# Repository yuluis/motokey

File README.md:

# MotoKey — Aftermarket E-Moto Security System

Encrypted keycard lock for electric motorcycles. Cut the power, pocket the key.

**Live site:** https://kindro.store
**Hardware design:** https://kindro.store/hardware-design.html

---

## What Is This

MotoKey is an aftermarket security system for electric mopeds/motorcycles/scooters. It's a small weatherproof box that wires inline with the battery and cuts power unless an encrypted key fob is nearby. No key = no power = bike doesn't move.

Every kit ships with:
- 1 lock box (mounts on bike, inline with battery)
- 2 encrypted key fobs (pocket/keychain sized)
- Mounting kit (bracket, zip ties, adhesive, wire terminals, heat shrink)
- Instruction card with QR link to install video

Two products:
| Product | Price | Key Difference |
|---------|-------|----------------|
| **MotoKey Basic** | $89 | AES-128, single relay, CR2032 fob, 30ft range |
| **MotoKey Enhanced** | $149 | AES-256, dual relay + tamper alert, USB-C fob, 50ft range, 3 fobs |

---

## Origin

This project started as a learning exercise between Luis and Julio on 2026-02-21. The goal: use AI (Claude) to go from idea to live website to hardware design in a single session.

**The conversation:**
- Julio builds aftermarket e-motos and wanted a keycard security system to sell
- Start with two versions: a basic remote and an enhanced remote
- Key fobs should be small (keychain/pocket dongle)
- The lock box connects to the battery with a simple power-cut circuit
- Must be weatherproof (outdoor bike use)
- Programming between keycard and hardware must be secured to prevent hacking
- Comes with 2 keys and a mounting kit

**What got built in this session:**
1. Product storefront website (static HTML/CSS/JS)
2. Full hardware architecture with real component selection
3. Security protocol design (AES-128 rolling codes, challenge-response)
4. Bill of materials with per-unit costs
5. Margin analysis proving profitability at $89/$149
6. Pushed to GitHub, deployed to production at kindro.store

---

## How It Works

### The Lock Box

Wires inline with the bike's main battery positive cable. Contains:
- **ATmega328P** microcontroller (same chip as Arduino)
- **SYN480R** 433MHz RF receiver
- **JQX-62F** 80A automotive relay (normally OPEN = locked)
- **LM2596** buck converter (48-72V battery → 5V logic)
- **AT24C256** EEPROM (stores up to 8 paired key records)
- Status LED + recessed pair button

The relay defaults to **open** (no power). When a valid key fob signal is received, the relay closes and power flows. When the key fob is out of range for 30 seconds, the relay opens and the bike is locked.

Cutting the wires doesn't help — the relay is normally open, so cutting anything just keeps the bike dead.

### The Key Fob

Small enough for a keychain. Contains:
- **ATtiny85** microcontroller (1.8μA sleep current)
- **SYN115** 433MHz RF transmitter
- **CR2032** coin cell battery (~18 month life)
- Single button

Press the button → MCU wakes from sleep → encrypts (counter + device ID) with the shared AES key → transmits 16-byte packet → goes back to sleep. Total active time: ~50ms.

### Security Protocol

**Pairing (one-time):**
1. Press PAIR button on lock box (LED blinks fast)
2. Press button on key fob
3. Lock box generates random 128-bit key
4. Key transfers to fob via physical contact (NFC/wired — can't intercept from distance)
5. Both devices store shared secret + set counter to 0

**Unlock (every use):**
1. Fob increments counter, encrypts (counter + fob ID) with shared key
2. Transmits encrypted packet over 433MHz
3. Lock box decrypts, verifies fob ID, checks counter > last seen
4. If valid: close relay (power on), start 30-sec timeout

**Why it's secure:**
- **Replay attack** → Fails. Counter already advanced. Old codes rejected.
- **Brute force** → AES-128 = 3.4×10³⁸ possible keys. Would take 10²² years at 1 billion attempts/sec.
- **Signal capture** → Every packet looks like random noise. No patterns.
- **Physical tamper** → Electronics potted in epoxy. Cracking the box destroys the circuits.
- **Wire bypass** → Relay is normally open. Cutting wires = bike stays dead.

---

## Economics

### Bill of Materials (at 100 units)

**Lock Box:** $10.80
| Component | Part | Cost |
|-----------|------|------|
| MCU | ATmega328P-AU | $1.40 |
| RF Receiver | SYN480R 433MHz | $0.50 |
| Relay | JQX-62F 80A | $2.80 |
| Relay Driver | 2N2222A + 1N4007 | $0.10 |
| Voltage Reg | LM2596 buck module | $0.80 |
| EEPROM | AT24C256 | $0.25 |
| Crystal | 16MHz + caps | $0.15 |
| LED + Button | Bicolor + tactile | $0.18 |
| Screw Terminals | 5mm pitch x2 | $0.30 |
| Wire Leads | 10AWG silicone x2 | $0.60 |
| Antenna | 17cm wire | $0.02 |
| PCB | 2-layer 50x40mm (JLCPCB) | $0.80 |
| Enclosure | ABS IP65 80x60x30mm | $1.80 |
| Cable Glands | PG7 nylon x2 | $0.20 |
| Potting | Urethane 2-part ~30ml | $0.50 |
| Misc | Caps, resistors, header | $0.40 |

**Key Fob (x1):** $2.37
| Component | Part | Cost |
|-----------|------|------|
| MCU | ATtiny85-20SU | $0.65 |
| RF Transmitter | SYN115 433MHz | $0.35 |
| Battery Holder | CR2032 SMD | $0.12 |
| Battery | CR2032 | $0.20 |
| Button | Tactile SMD 4x4mm | $0.05 |
| PCB | 2-layer 35x20mm | $0.40 |
| Enclosure | ABS fob case + keyring | $0.45 |
| Misc | Caps, resistors | $0.15 |

**Mounting Kit:** $1.60 | **Packaging:** $1.20

### Margin Analysis

| | Basic ($89) | Enhanced ($149) |
|---|---|---|
| BOM + materials | $18.34 | $31.10 |
| Assembly + QC | $5.00 | $8.25 |
| **Total COGS** | **$23.34** | **$39.35** |
| **Gross margin** | **$65.66 (73.8%)** | **$109.65 (73.6%)** |

At even 10 hand-built units ($30 COGS), the Basic still clears $59/unit.

---

## Next Steps for Julio

### Phase 1: Prototype (Weekends 1-2) — ~$35

Buy from Amazon/AliExpress:
- Arduino Nano (ATmega328P dev board) — $5
- 433MHz TX/RX module pair — $3
- 80A automotive relay module — $6
- ATtiny85 dev board (Digispark) — $4
- LM2596 buck converter module — $2
- Breadboard + jumper wires — $5
- CR2032 battery + holder — $2
- Push buttons + LEDs + resistors — $3
- ABS project box — $3
- Key fob cases (2-pack) — $2

Also need (one-time): USB-ASP programmer (~$8), soldering iron if you don't have one.

**Weekend 1: Proof of concept**
- Wire Arduino Nano + relay on breadboard
- Wire ATtiny85 + 433MHz TX on second breadboard
- Write basic TX/RX code (no encryption yet)
- Goal: press fob button → relay clicks → LED lights up

**Weekend 2: Add security**
- Add AES-128 library to both MCUs (use `tiny-AES-c` library)
- Hardcode a shared test key
- Implement rolling counter
- Verify that replaying a captured signal is rejected

### Phase 2: Complete Product (Weekends 3-4)

**Weekend 3: Pairing + polish**
- Add pair button logic on lock box
- Implement key exchange (wired connection for prototype)
- Add LED status states (green=unlocked, red=locked, blink=pairing)
- Add 30-second auto-lock timeout
- Add EEPROM storage for paired keys (support up to 8)

**Weekend 4: Enclosure + real test**
- Solder onto perfboard (replace breadboard)
- Mount in ABS project box with cable glands
- Fit fob circuit into key fob case
- Test with actual e-moto (or 48V bench supply)
- Range test through walls (target: 20-30m)
- Seal with potting compound

### Phase 3: First Production Run (Week 5-6)

- Order custom PCBs from JLCPCB (5-day turnaround, ~$0.80/board at 100 qty)
- Order components from LCSC (ships with PCBs)
- Assemble 10 units
- Create install video (phone camera is fine, post to YouTube)
- Print instruction cards with QR code to video

### Phase 4: Website + Sales

- Update kindro.store with real product photos
- Add Stripe payment integration (or start with PayPal/Venmo for simplicity)
- Post on e-moto forums, Facebook groups, Reddit r/ebikes r/emotorcycles
- List on eBay/Amazon if volume justifies it

---

## Plan to Sell the First 10 Units

### Target Customer
Owners of Chinese-brand electric mopeds/scooters (Onyx, Monday Motorbikes, Super73-adjacent, Sur-Ron, Talaria, generic 48V-72V e-motos) who currently have zero theft protection.

### Pricing Strategy
- **Launch price: $79 Basic / $129 Enhanced** (introductory discount)
- After first 10 units and reviews: raise to $89 / $149
- Bundle deal: Basic + Extra Fob 2-pack for $99

### Sales Channels (ranked by effort vs return)

**1. E-moto Facebook groups (free, highest conversion)**
- Join: "Sur-Ron Owners Group", "Onyx Motorbikes Owners", "Electric Motorcycle Riders", "E-bike Security"
- Post a demo video: "I made an aftermarket kill switch for my [bike]. Press fob = power. Walk away = dead. $79."
- Engage with theft complaint posts (there are many)
- Offer first 5 buyers a discount for honest reviews

**2. Reddit (free, wide reach)**
- r/ebikes (750K+ members), r/surron, r/emotorcycles, r/ElectricScooters
- Post as "I built this" with demo video/gif
- Link to site in comments (not title — Reddit hates direct sales posts)

**3. Local e-moto shops / repair shops**
- Leave 2 demo units at local shops on consignment
- They sell for $89, keep $15 commission
- Julio's existing network of people who build aftermarket e-motos

**4. eBay listing**
- Low effort to set up
- "Electric Motorcycle Security Kill Switch - Encrypted Key Fob - Aftermarket Anti-Theft"
- eBay takes ~13% but handles payments and provides buyer trust

**5. YouTube install video**
- Film installing MotoKey on an actual e-moto (3-5 min)
- Title: "DIY Anti-Theft for Electric Motorcycles - $79 Kill Switch Install"
- Description links to kindro.store
- This becomes the long-tail discovery channel

### First 10 Units — Concrete Plan

| Unit | Channel | Price | Notes |
|------|---------|-------|-------|
| 1 | Personal use / demo | $0 | Install on Julio's bike for demo videos |
| 2 | Consignment at local shop | $89 | Leave with a shop Julio trusts |
| 3-5 | Facebook groups | $79 | Launch price, ask for reviews |
| 6-7 | Reddit posts | $79 | Link to kindro.store |
| 8 | eBay | $89 | Test marketplace demand |
| 9-10 | Word of mouth / referral | $79 | Offer $10 referral to early buyers |

### Revenue from first 10

| | Units | Revenue |
|---|---|---|
| Demo unit | 1 | $0 |
| At $79 | 7 | $553 |
| At $89 | 2 | $178 |
| **Total** | **10** | **$731** |
| COGS (10 units @ ~$30 hand-built) | | -$300 |
| **Net profit** | | **$431** |

That $431 funds the next batch of 25-50 units at proper PCB pricing, which drops COGS to ~$23/unit and margin jumps to 74%.

### Marketing Assets Needed
1. **Demo video** (30 sec): Press fob → bike powers on. Walk away → bike dies. Film on actual e-moto.
2. **Install video** (3-5 min): Full install process. Phone camera is fine.
3. **Product photos**: Lock box, fobs, complete kit in packaging. Natural light, clean background.
4. **One-liner**: "Encrypted kill switch for your e-moto. $79. Two keys included."

---

## Tech Stack (Website)

- Static HTML + CSS + JavaScript (no framework, no build step)
- Hosted on DigitalOcean VPS behind nginx
- Domain: kindro.store (SSL via Let's Encrypt)

---

## Repository Structure

```
motokey/
├── index.html              # Product storefront
├── style.css               # Storefront styles
├── app.js                  # Cart + FAQ interactivity
├── hardware-design.html    # Full hardware architecture document
├── .gitignore
└── README.md               # This file
```

---

## Built With

This entire project — website, hardware architecture, security protocol, BOM, margin analysis, and go-to-market plan — was designed in a single AI-assisted session using [Claude Code](https://claude.com/claude-code).

The goal was to demonstrate how to go from conversation to live product in one sitting:
1. Discussed the idea → 2. Built the website → 3. Pushed to GitHub → 4. Deployed to production → 5. Designed the hardware → 6. Wrote the business plan

Total time: one session. Total code written by hand: zero.

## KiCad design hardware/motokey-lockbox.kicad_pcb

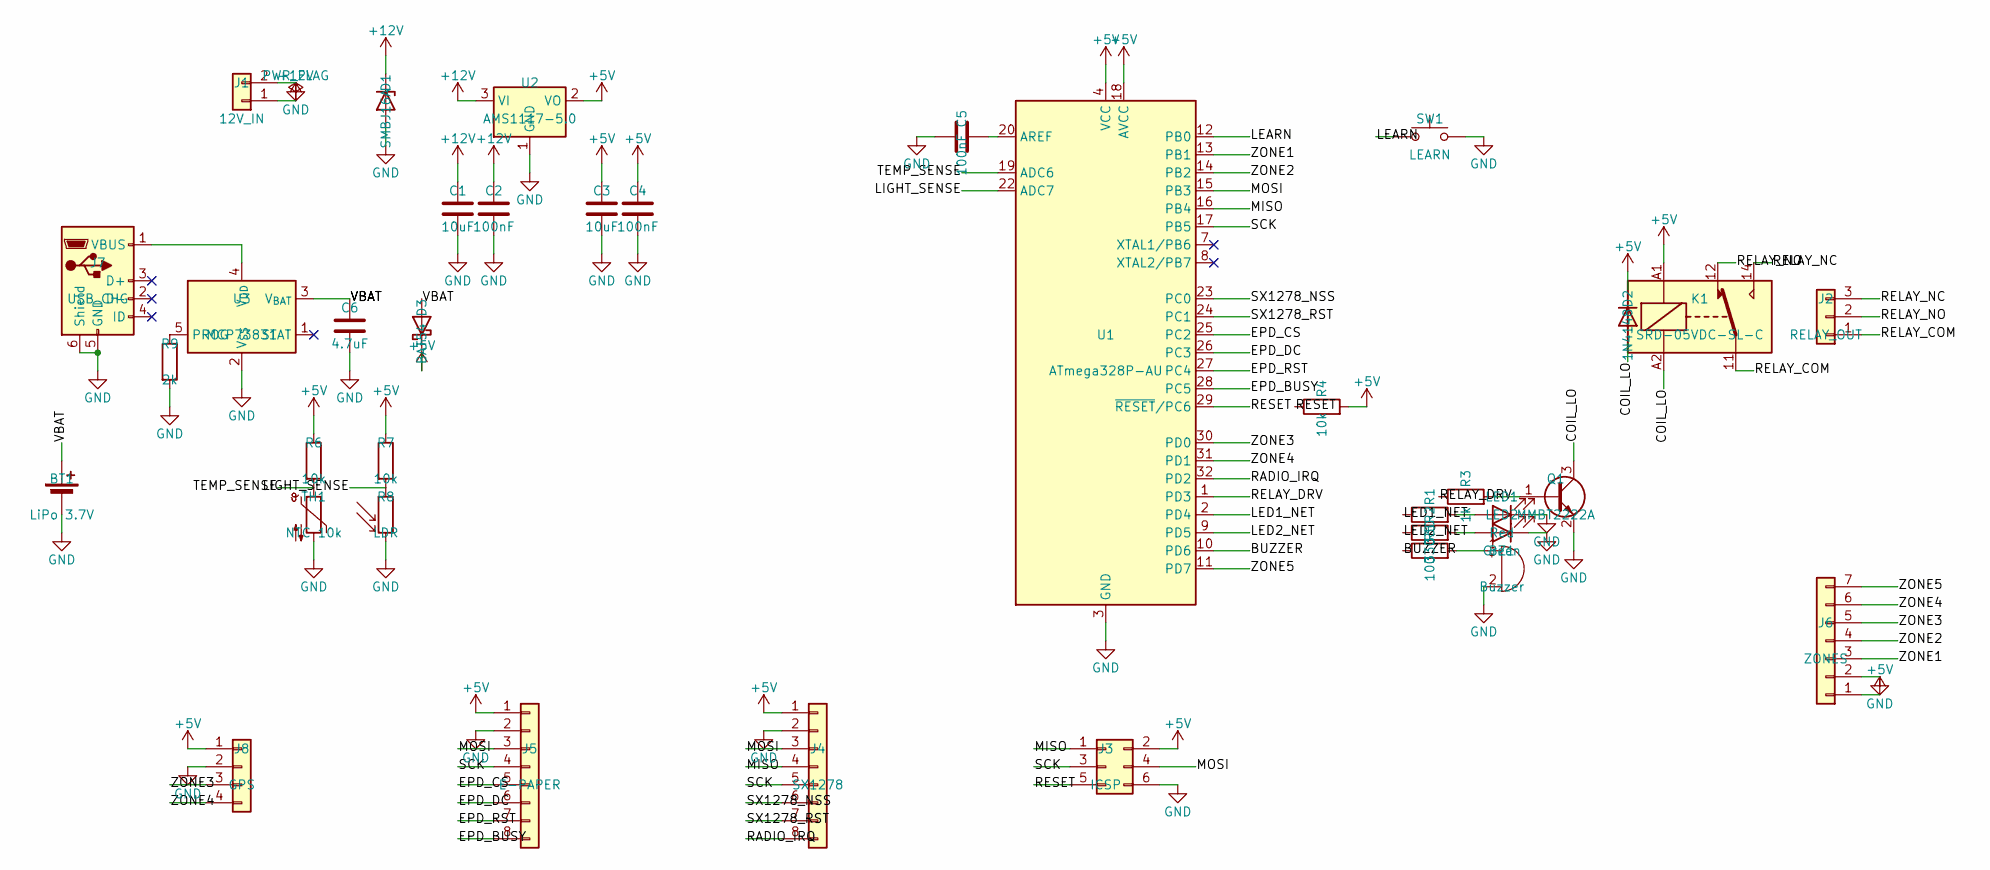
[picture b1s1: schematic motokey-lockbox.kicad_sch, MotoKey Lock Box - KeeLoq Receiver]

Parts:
BT1: LiPo 3.7V; BatteryHolder_Keystone_1042_1x18650
BZ1: Buzzer; Buzzer_12x9.5RM7.6
C1, C3: 10uF; C_0805_2012Metric
C2, C4, C5: 100nF; C_0805_2012Metric
C6: 4.7uF; C_0805_2012Metric
D1: SMBJ16A; D_SMB_Handsoldering
D2: 1N4148; D_SOD-123
D3: BAT54; D_SOD-123
J1: 12V_IN; PinHeader_1x02_P2.54mm_Vertical
J2: RELAY_OUT; PinHeader_1x03_P2.54mm_Vertical
J3: ICSP; PinHeader_2x03_P2.54mm_Vertical
J4: SX1278; PinHeader_1x08_P2.54mm_Vertical
J5: E-PAPER; PinHeader_1x08_P2.54mm_Vertical
J6: ZONES; PinHeader_1x07_P2.54mm_Vertical
J7: USB_CHG; USB_Micro-B_Molex-105017-0001
J8: GPS; PinHeader_1x04_P2.54mm_Vertical
K1: SRD-05VDC-SL-C; Relay_SPDT_Finder_40.11
LED1: Red; LED_0805_2012Metric
LED2: Green; LED_0805_2012Metric
Q1: MMBT2222A; SOT-23
R1, R2: 330; R_0805_2012Metric
R3: 1k; R_0805_2012Metric
R4, R6, R7: 10k; R_0805_2012Metric
R5: 100; R_0805_2012Metric
R8: LDR; R_0805_2012Metric
R9: 2k; R_0805_2012Metric
SW1: LEARN; SW_SPST_PTS645Sx43SMTR92
TH1: NTC 10k; R_0805_2012Metric
U1: ATmega328P-AU; TQFP-32_7x7mm_P0.8mm
U2: AMS1117-5.0; SOT-223-3_TabPin2
U3: MCP73831; SOT-23-5

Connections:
+5V: C3.1, C4.1, D2.1 (K), D3.1 (K), J3.2, J4.1, J5.1, J6.1, J8.1, K1.A1, R4.2, R6.1, R7.1, U1.4 (VCC), U1.6 (VCC), U1.18 (AVCC), U2.2 (VO)
+12V: C1.1, C2.1, D1.1 (K), J1.1, U2.3 (VI)
/BUZZER: R5.1, U1.10 (PD6)
/COIL_LO: D2.2 (A), K1.A2, Q1.3 (C)
/EPD_BUSY: J5.8, U1.28 (PC5)
/EPD_CS: J5.5, U1.25 (PC2)
/EPD_DC: J5.6, U1.26 (PC3)
/EPD_RST: J5.7, U1.27 (PC4)
/LEARN: SW1.1, U1.12 (PB0)
/LED1_NET: R1.1, U1.2 (PD4)
/LED2_NET: R2.1, U1.9 (PD5)
/LIGHT_SENSE: R7.2, R8.1, U1.22 (ADC7)
/MISO: J3.1, J4.4, U1.16 (PB4)
/MOSI: J3.4, J4.3, J5.3, U1.15 (PB3)
/RADIO_IRQ: J4.8, U1.32 (PD2)
/RELAY_COM: J2.1, K1.11
/RELAY_DRV: R3.1, U1.1 (PD3)
/RELAY_NC: J2.3, K1.14
/RELAY_NO: J2.2, K1.12
/RESET: J3.5, R4.1, U1.29 (~RESET/PC6)
/SCK: J3.3, J4.5, J5.4, U1.17 (PB5)
/SX1278_NSS: J4.6, U1.23 (PC0)
/SX1278_RST: J4.7, U1.24 (PC1)
/TEMP_SENSE: R6.2, TH1.1, U1.19 (ADC6)
/VBAT: BT1.1 (+), C6.1, D3.2 (A), U3.3 (V_{BAT})
/ZONE1: J6.3, U1.13 (PB1)
/ZONE2: J6.4, U1.14 (PB2)
/ZONE3: J6.5, J8.3, U1.30 (PD0)
/ZONE4: J6.6, J8.4, U1.31 (PD1)
/ZONE5: J6.7, U1.11 (PD7)
GND: BT1.2 (-), BZ1.2 (-), C1.2, C2.2, C3.2, C4.2, C5.1, C6.2, D1.2 (A), J1.2, J3.6, J4.2, J5.2, J6.2, J7.5 (GND), J7.6 (Shield), J8.2, LED1.1 (K), LED2.1 (K), Q1.2 (E), R8.2, R9.2, SW1.2, TH1.2, U1.3 (GND), U1.5 (GND), U1.21 (GND), U2.1 (GND), U3.2 (V_{SS})
unnamed: BZ1.1 (+), R5.2
unnamed: J7.1 (VBUS), U3.4 (V_{DD})
unnamed: LED1.2 (A), R1.2
unnamed: LED2.2 (A), R2.2
unnamed: Q1.1 (B), R3.2
unnamed: C5.2, U1.20 (AREF)
unnamed: R9.1, U3.5 (PROG)

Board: 2 copper layers, 41 parts (0 on the bottom side), 38 nets, no tracks yet.

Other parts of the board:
MH1, MH2, MH3, MH4: MountingHole; MountingHole_3.2mm_M3

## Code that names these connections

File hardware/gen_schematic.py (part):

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  D3: Schottky diode (battery → +5V power path)
  BT1: LiPo battery cell (3.7V)
  LED1/LED2: status LEDs (red=armed, green=unlocked)
  BZ1: passive piezo buzzer (PWM on PD6/OC0A)
  J4: SX1278 LoRa/ASK radio module (8-pin header)
  J5: 1.54" e-paper display (8-pin header, optional)
  J6: Zone inputs for NO/NC contact sensors (7-pin header)
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    u1_adc7 = u1l(22.86)         # ADC7 — LIGHT_SENSE

    # Right-side port pins
    u1_pb0 = u1r(30.48)   # PB0 — LEARN
    u1_pb1 = u1r(27.94)   # PB1 — ZONE1
    u1_pb2 = u1r(25.4)    # PB2 — ZONE2
    u1_pb3 = u1r(22.86)   # PB3 — MOSI
    u1_pb4 = u1r(20.32)   # PB4 — MISO
    u1_pb5 = u1r(17.78)   # PB5 — SCK
    u1_xtal1 = u1r(15.24) # XTAL1 — NC
    u1_xtal2 = u1r(12.7)  # XTAL2 — NC
    u1_pc0 = u1r(7.62)    # PC0 — SX1278_NSS
    u1_pc1 = u1r(5.08)    # PC1 — SX1278_RST
    u1_pc2 = u1r(2.54)    # PC2 — EPD_CS
    u1_pc3 = u1r(0)       # PC3 — EPD_DC
    u1_pc4 = u1r(-2.54)   # PC4 — EPD_RST
    u1_pc5 = u1r(-5.08)   # PC5 — EPD_BUSY
    u1_reset = u1r(-7.62) # ~RESET/PC6
    u1_pd0 = u1r(-12.7)   # PD0 — ZONE3
    u1_pd1 = u1r(-15.24)  # PD1 — ZONE4
    u1_pd2 = u1r(-17.78)  # PD2 — RADIO_IRQ (INT0)
    u1_pd3 = u1r(-20.32)  # PD3 — RELAY_DRV
    u1_pd4 = u1r(-22.86)  # PD4 — LED1
    u1_pd5 = u1r(-25.4)   # PD5 — LED2
    u1_pd6 = u1r(-27.94)  # PD6 — BUZZER (OC0A)
    u1_pd7 = u1r(-30.48)  # PD7 — ZONE5

    # Set Q1y to match PD3 for horizontal R3→Q1 wire
    Q1y = u1_pd3[1]

    components.append(s_comp(
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        elements.append(s_label(name, pin[0] - 5.08, pin[1], 180))

    # Left-side MCU signal labels (ADC6, ADC7)
    label_left(u1_adc6, "TEMP_SENSE")
    label_left(u1_adc7, "LIGHT_SENSE")

    # Right-side MCU signal labels
    label_right(u1_pb0, "LEARN")
    label_right(u1_pb1, "ZONE1")
    label_right(u1_pb2, "ZONE2")
    label_right(u1_pb3, "MOSI")
    label_right(u1_pb4, "MISO")
    label_right(u1_pb5, "SCK")
    label_right(u1_reset, "RESET")
    label_right(u1_pc0, "SX1278_NSS")
    label_right(u1_pc1, "SX1278_RST")
    label_right(u1_pc2, "EPD_CS")
    label_right(u1_pc3, "EPD_DC")
    label_right(u1_pc4, "EPD_RST")
    label_right(u1_pc5, "EPD_BUSY")
    label_right(u1_pd0, "ZONE3")
    label_right(u1_pd1, "ZONE4")
    label_right(u1_pd2, "RADIO_IRQ")
    label_right(u1_pd3, "RELAY_DRV")
    label_right(u1_pd4, "LED1_NET")
    label_right(u1_pd5, "LED2_NET")
    label_right(u1_pd6, "BUZZER")
    label_right(u1_pd7, "ZONE5")

    # ---- U2: AMS1117-5.0 LDO ----
    # Pins: VI(3) at (-7.62,0), GND(1) at (0,-7.62), VO(2) at (7.62,0)
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        "LED1 current limit"))
    r1_p1 = pxy(R1x, R1y, 0, 3.81, 90)
    r1_p2 = pxy(R1x, R1y, 0, -3.81, 90)
    elements.append(s_label("LED1_NET", r1_p1[0], r1_p1[1]))

    LED1x = R1x + 4*G
    components.append(s_comp("Device:LED", "LED1", "Red",
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        "LED2 current limit"))
    r2_p1 = pxy(R2x, R2y, 0, 3.81, 90)
    r2_p2 = pxy(R2x, R2y, 0, -3.81, 90)
    elements.append(s_label("LED2_NET", r2_p1[0], r2_p1[1]))

    LED2x = R2x + 4*G
    components.append(s_comp("Device:LED", "LED2", "Green",
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        "Buzzer current limit"))
    r5_p1 = pxy(R5x, R5y, 0, 3.81, 90)   # left
    r5_p2 = pxy(R5x, R5y, 0, -3.81, 90)  # right
    elements.append(s_label("BUZZER", r5_p1[0], r5_p1[1]))

    # BZ1: passive piezo buzzer (vertical, pin1(+) aligns with R5 pin2)
    BZ1x, BZ1y = 82*G, R5y + 2.54
    components.append(s_comp("Device:Buzzer", "BZ1", "Buzzer",
        "Buzzer_Beeper:Buzzer_12x9.5RM7.6", BZ1x, BZ1y, 0, ["1", "2"],
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        "Relay driver base resistor"))
    r3_p1 = pxy(R3x, R3y, 0, 3.81, 90)
    r3_p2 = pxy(R3x, R3y, 0, -3.81, 90)
    elements.append(s_label("RELAY_DRV", r3_p1[0], r3_p1[1]))

    # ---- Q1: MMBT2222A NPN relay driver ----
    # Pins: B at (-5.08,0), C at (2.54,5.08), E at (2.54,-5.08)
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    add_5v(k1_a1[0], k1_a1[1] - 2.54)
    # K1.A2 (coil-) → Q1.collector via COIL_LO net
    elements.append(s_wire(*k1_a2, k1_a2[0], k1_a2[1] + 2.54))
    elements.append(s_label("COIL_LO", k1_a2[0], k1_a2[1] + 2.54, 270))
    elements.append(s_wire(*q1_c, q1_c[0], q1_c[1] - 2.54))
    elements.append(s_label("COIL_LO", q1_c[0], q1_c[1] - 2.54, 90))

    # ---- D2: 1N4148 flyback diode ----
    D2x, D2y = K1x - 4*G, K1y  # left of relay coil
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    add_5v(d2_k[0], d2_k[1] - 2.54)
    # D2 anode → COIL_LO
    elements.append(s_wire(*d2_a, d2_a[0], d2_a[1] + 2.54))
    elements.append(s_label("COIL_LO", d2_a[0], d2_a[1] + 2.54, 270))

    # ---- J2: Relay output (3-pin screw terminal) ----
    J2x, J2y = 100*G, K1y
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
    # Connect relay switch pins to J2 via labels
    elements.append(s_wire(*k1_11, k1_11[0] + 2.54, k1_11[1]))
    elements.append(s_label("RELAY_COM", k1_11[0] + 2.54, k1_11[1]))
    elements.append(s_wire(*j2_p1, j2_p1[0] + 2.54, j2_p1[1]))
    elements.append(s_label("RELAY_COM", j2_p1[0] + 2.54, j2_p1[1]))

    elements.append(s_wire(*k1_12, k1_12[0] + 2.54, k1_12[1]))
    elements.append(s_label("RELAY_NO", k1_12[0] + 2.54, k1_12[1]))
    elements.append(s_wire(*j2_p2, j2_p2[0] + 2.54, j2_p2[1]))
    elements.append(s_label("RELAY_NO", j2_p2[0] + 2.54, j2_p2[1]))

    elements.append(s_wire(*k1_14, k1_14[0] + 2.54, k1_14[1]))
    elements.append(s_label("RELAY_NC", k1_14[0] + 2.54, k1_14[1]))
    elements.append(s_wire(*j2_p3, j2_p3[0] + 2.54, j2_p3[1]))
    elements.append(s_label("RELAY_NC", j2_p3[0] + 2.54, j2_p3[1]))

    # ---- J3: ICSP header (2x3) ----
    J3x, J3y = 60*G, 67*G
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    elements.append(s_label("SCK", j4_pins[5][0] - 5.08, j4_pins[5][1]))
    # Pin 6: NSS (chip select, active low)
    elements.append(s_wire(*j4_pins[6], j4_pins[6][0] - 5.08, j4_pins[6][1]))
    elements.append(s_label("SX1278_NSS", j4_pins[6][0] - 5.08, j4_pins[6][1]))
    # Pin 7: RESET
    elements.append(s_wire(*j4_pins[7], j4_pins[7][0] - 5.08, j4_pins[7][1]))
    elements.append(s_label("SX1278_RST", j4_pins[7][0] - 5.08, j4_pins[7][1]))
    # Pin 8: DIO0 (interrupt)
    elements.append(s_wire(*j4_pins[8], j4_pins[8][0] - 5.08, j4_pins[8][1]))
    elements.append(s_label("RADIO_IRQ", j4_pins[8][0] - 5.08, j4_pins[8][1]))

    # ---- J5: 1.54" E-Paper display (optional, 8-pin header) ----
    # Pin assignment: 1=VCC, 2=GND, 3=MOSI, 4=SCK, 5=EPD_CS, 6=EPD_DC, 7=EPD_RST, 8=EPD_BUSY
    J5x, J5y = 28*G, 67*G
    components.append(s_comp(
        "Connector_Generic:Conn_01x08", "J5", "E-PAPER",
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    # Pin 4: SCK (shared SPI bus)
    elements.append(s_wire(*j5_pins[4], j5_pins[4][0] - 5.08, j5_pins[4][1]))
    elements.append(s_label("SCK", j5_pins[4][0] - 5.08, j5_pins[4][1]))
    # Pin 5: EPD_CS (chip select)
    elements.append(s_wire(*j5_pins[5], j5_pins[5][0] - 5.08, j5_pins[5][1]))
    elements.append(s_label("EPD_CS", j5_pins[5][0] - 5.08, j5_pins[5][1]))
    # Pin 6: EPD_DC (data/command)
    elements.append(s_wire(*j5_pins[6], j5_pins[6][0] - 5.08, j5_pins[6][1]))
    elements.append(s_label("EPD_DC", j5_pins[6][0] - 5.08, j5_pins[6][1]))
    # Pin 7: EPD_RST (reset)
    elements.append(s_wire(*j5_pins[7], j5_pins[7][0] - 5.08, j5_pins[7][1]))
    elements.append(s_label("EPD_RST", j5_pins[7][0] - 5.08, j5_pins[7][1]))
    # Pin 8: EPD_BUSY (busy signal, input)
    elements.append(s_wire(*j5_pins[8], j5_pins[8][0] - 5.08, j5_pins[8][1]))
    elements.append(s_label("EPD_BUSY", j5_pins[8][0] - 5.08, j5_pins[8][1]))

    # ---- RT1 + R6: NTC thermistor voltage divider (TEMP_SENSE on ADC6) ----
    # +5V → R6 (10k) → junction → RT1 (NTC 10k) → GND
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    elements.append(s_wire(*rt1_p2, rt1_p2[0], rt1_p2[1] + 2.54))
    add_gnd(rt1_p2[0], rt1_p2[1] + 2.54)
    # Junction label at R6.pin2 = RT1.pin1
    elements.append(s_label("TEMP_SENSE", r6_p2[0] - 5.08, r6_p2[1], 180))
    elements.append(s_wire(*r6_p2, r6_p2[0] - 5.08, r6_p2[1]))

    # ---- R_LDR + R7: Photoresistor voltage divider (LIGHT_SENSE on ADC7) ----
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    elements.append(s_wire(*ldr_p2, ldr_p2[0], ldr_p2[1] + 2.54))
    add_gnd(ldr_p2[0], ldr_p2[1] + 2.54)
    # Junction label
    elements.append(s_label("LIGHT_SENSE", r7_p2[0] - 5.08, r7_p2[1], 180))
    elements.append(s_wire(*r7_p2, r7_p2[0] - 5.08, r7_p2[1]))

    # ---- J6: Zone inputs for NO/NC contact sensors (7-pin header) ----
    # Pin assignment: 1=+5V, 2=GND, 3=ZONE1, 4=ZONE2, 5=ZONE3, 6=ZONE4, 7=ZONE5
    # Each zone uses MCU internal pullup. Sensor wires between ZONEx and GND.
    J6x, J6y = 100*G, 60*G
    components.append(s_comp(
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    # Pin 2: GND (sensor return)
    elements.append(s_wire(*j6_pins[2], j6_pins[2][0] + 2.54, j6_pins[2][1]))
    add_gnd(j6_pins[2][0] + 2.54, j6_pins[2][1])
    # Pins 3-7: ZONE1-ZONE5 via net labels
    for i, zone in enumerate(["ZONE1", "ZONE2", "ZONE3", "ZONE4", "ZONE5"], start=3):
        elements.append(s_wire(*j6_pins[i], j6_pins[i][0] + 5.08, j6_pins[i][1]))
        elements.append(s_label(zone, j6_pins[i][0] + 5.08, j6_pins[i][1]))
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        "Learn/pair button"))
    sw1_p1 = pxy(SW1x, SW1y, -5.08, 0, 0)
    sw1_p2 = pxy(SW1x, SW1y, 5.08, 0, 0)
    elements.append(s_label("LEARN", sw1_p1[0] - 2.54, sw1_p1[1]))
    elements.append(s_wire(*sw1_p1, sw1_p1[0] - 2.54, sw1_p1[1]))
    elements.append(s_wire(*sw1_p2, sw1_p2[0] + 2.54, sw1_p2[1]))
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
